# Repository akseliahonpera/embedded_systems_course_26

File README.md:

# embedded_systems_course_26
Repo for embedded systems course project in uni Oulu. Project theme is a drone system.

asdf

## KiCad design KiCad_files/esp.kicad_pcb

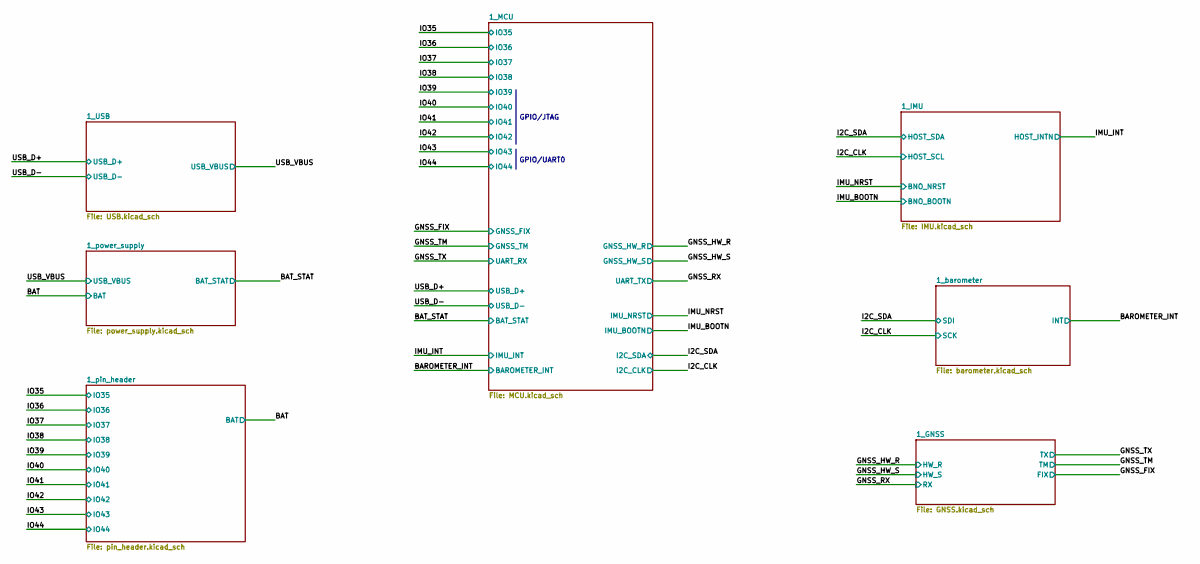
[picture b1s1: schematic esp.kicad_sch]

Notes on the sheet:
GPIO/JTAG
GPIO/UART0

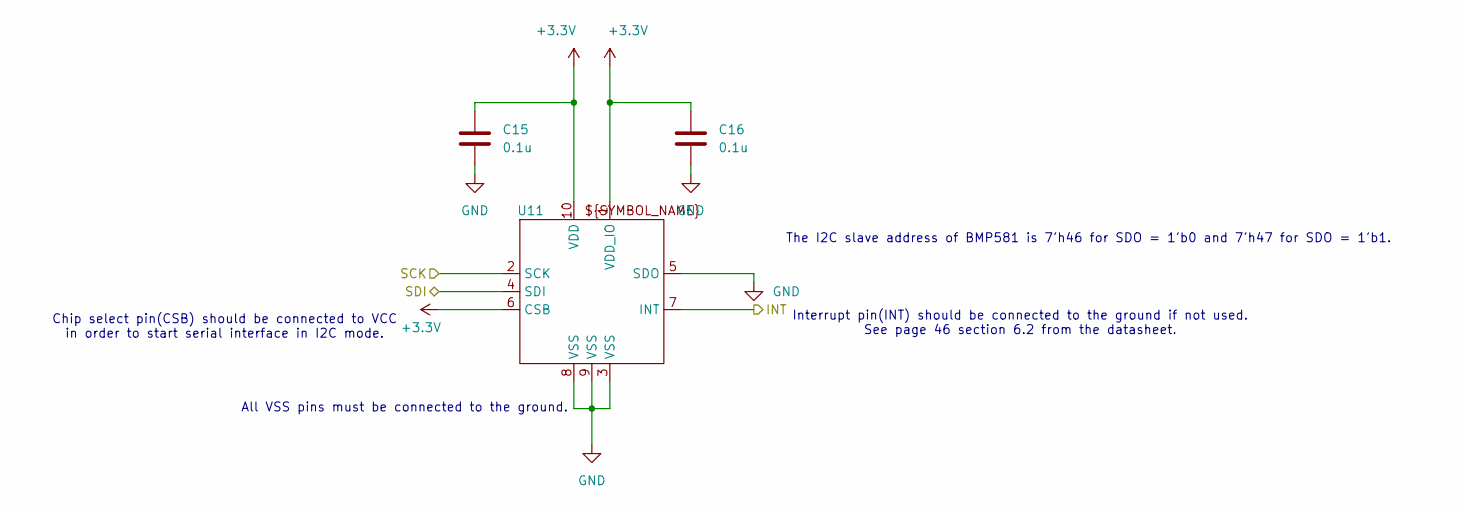
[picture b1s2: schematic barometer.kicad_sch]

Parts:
C15, C16: 0.1u; C_0805_2012Metric_Pad1.18x1.45mm_HandSolder; DigiKey 720-1754-1-ND
U11: QFN10_BMP581_BOS; DigiKey 828-BMP581CT-ND

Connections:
+3.3V: C15.1, C16.1, U11.1 (VDD_IO), U11.6 (CSB), U11.10 (VDD); also elsewhere on the board
/BAROMETER_INT: U11.7 (INT); also elsewhere on the board
/I2C_CLK: U11.2 (SCK); also elsewhere on the board
/I2C_SDA: U11.4 (SDI); also elsewhere on the board
GND: C15.2, C16.2, U11.3 (VSS), U11.5 (SDO), U11.8 (VSS), U11.9 (VSS); also elsewhere on the board

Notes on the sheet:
Chip select pin(CSB) should be connected to VCC in order to start serial interface in I2C mode.
The I2C slave address of BMP581 is 7'h46 for SDO = 1'b0 and 7'h47 for SDO = 1'b1.
All VSS pins must be connected to the ground.
Interrupt pin(INT) should be connected to the ground if not used. See page 46 section 6.2 from the datasheet.

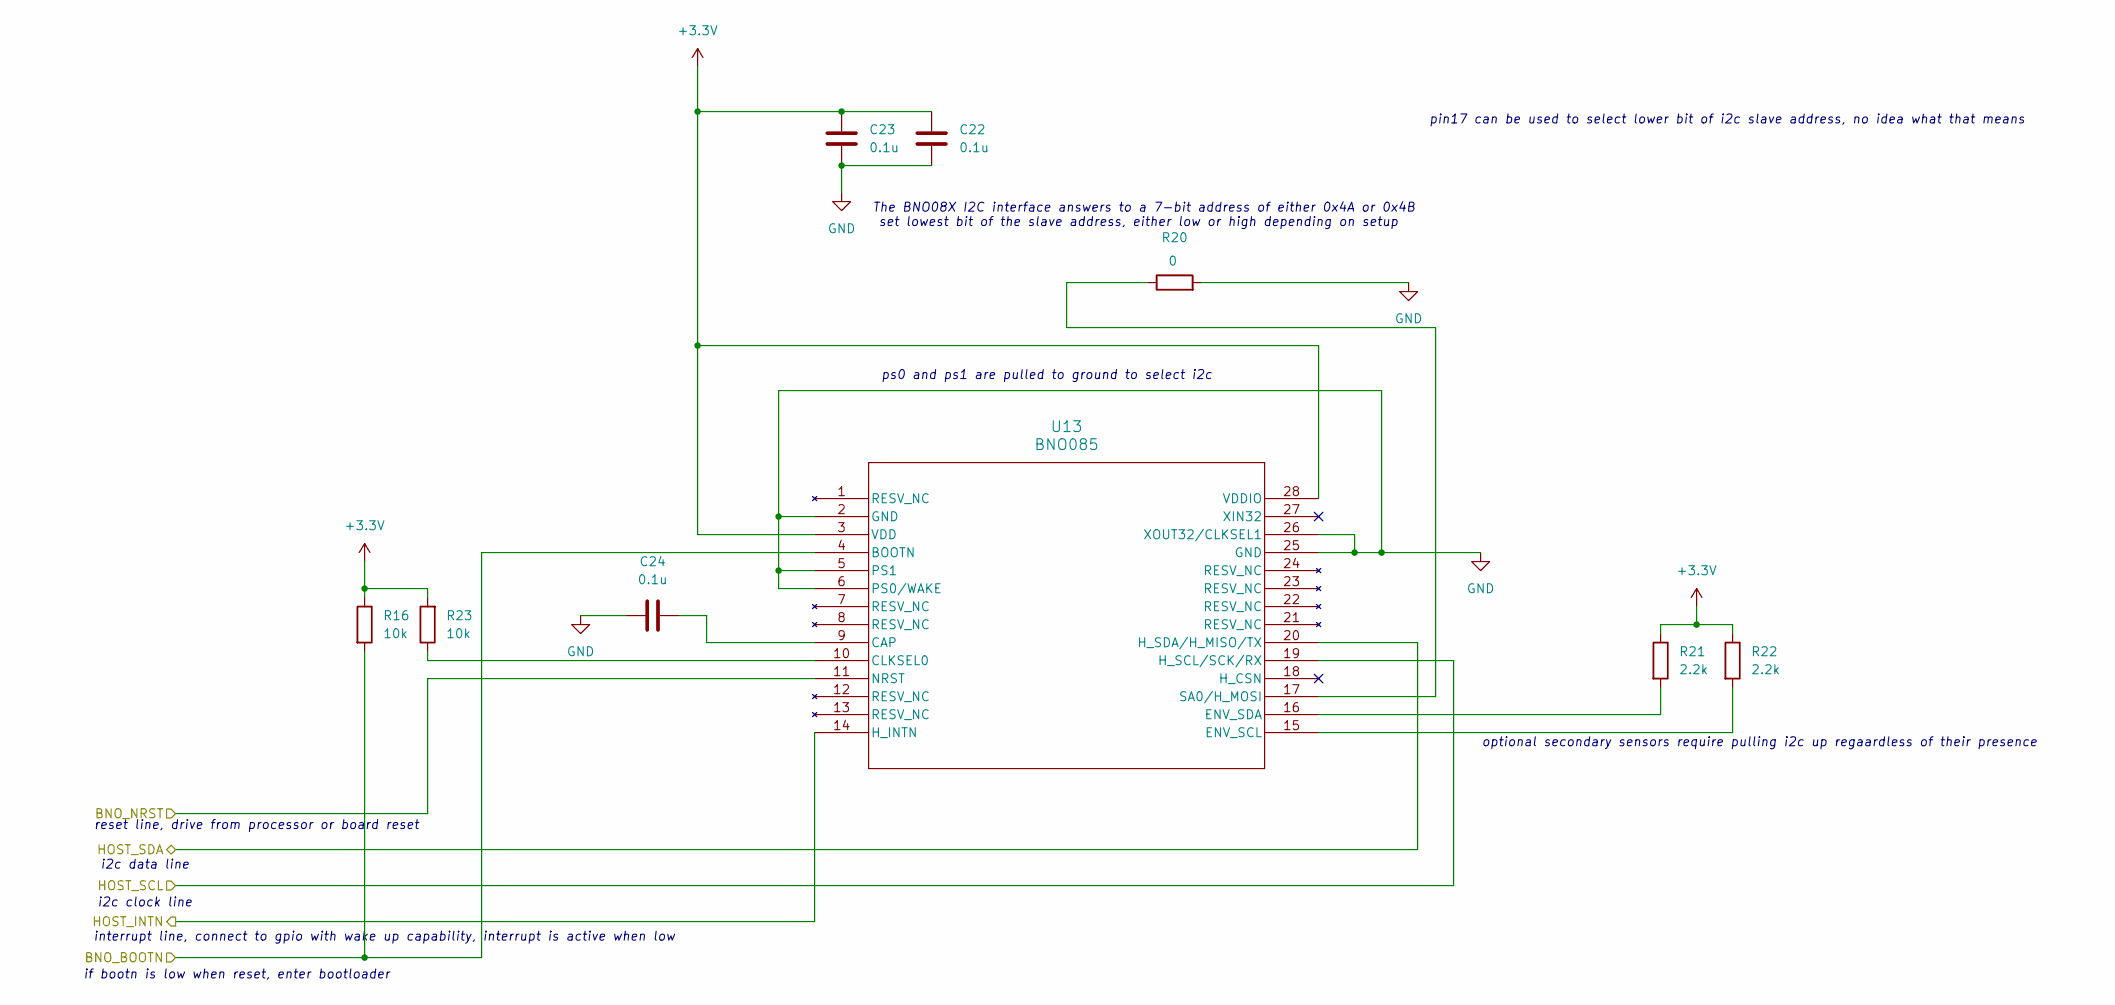
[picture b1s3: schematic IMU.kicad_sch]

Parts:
C22, C23, C24: 0.1u; C_0805_2012Metric_Pad1.18x1.45mm_HandSolder; DigiKey 720-1754-1-ND
R16, R23: 10k; R_0805_2012Metric_Pad1.20x1.40mm_HandSolder; DigiKey 541-10.0KCCT-ND
R20: 0; R_0805_2012Metric_Pad1.20x1.40mm_HandSolder
R21, R22: 2.2k; R_0805_2012Metric_Pad1.20x1.40mm_HandSolder; DigiKey 311-2.20KCRCT-ND
U13: BNO085; DigiKey 1888-1006-1-ND

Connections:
+3.3V: C22.1, C23.1, R16.1, R21.1, R22.1, R23.2, U13.3 (VDD), U13.28 (VDDIO); also elsewhere on the board
/I2C_CLK: U13.19 (H_SCL/SCK/RX); also elsewhere on the board
/I2C_SDA: U13.20 (H_SDA/H_MISO/TX); also elsewhere on the board
/IMU_BOOTN: R16.2, U13.4 (BOOTN); also elsewhere on the board
/IMU_INT: U13.14 (H_INTN); also elsewhere on the board
/IMU_NRST: U13.11 (NRST); also elsewhere on the board
GND: C22.2, C23.2, C24.2, R20.2, U13.2 (GND), U13.5 (PS1), U13.6 (PS0/WAKE), U13.25 (GND), U13.26 (XOUT32/CLKSEL1); also elsewhere on the board
unnamed: C24.1, U13.9 (CAP)
unnamed: R23.1, U13.10 (CLKSEL0)
unnamed: R22.2, U13.15 (ENV_SCL)
unnamed: R21.2, U13.16 (ENV_SDA)
unnamed: R20.1, U13.17 (SA0/H_MOSI)

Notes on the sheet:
ps0 and ps1 are pulled to ground to select i2c
optional secondary sensors require pulling i2c up regaardless of their presence
pin17 can be used to select lower bit of i2c slave address, no idea what that means
i2c clock line
i2c data line
reset line, drive from processor or board reset
set lowest bit of the slave address, either low or high depending on setup
interrupt line, connect to gpio with wake up capability, interrupt is active when low
if bootn is low when reset, enter bootloader
The BNO08X I2C interface answers to a 7-bit address of either 0x4A or 0x4B

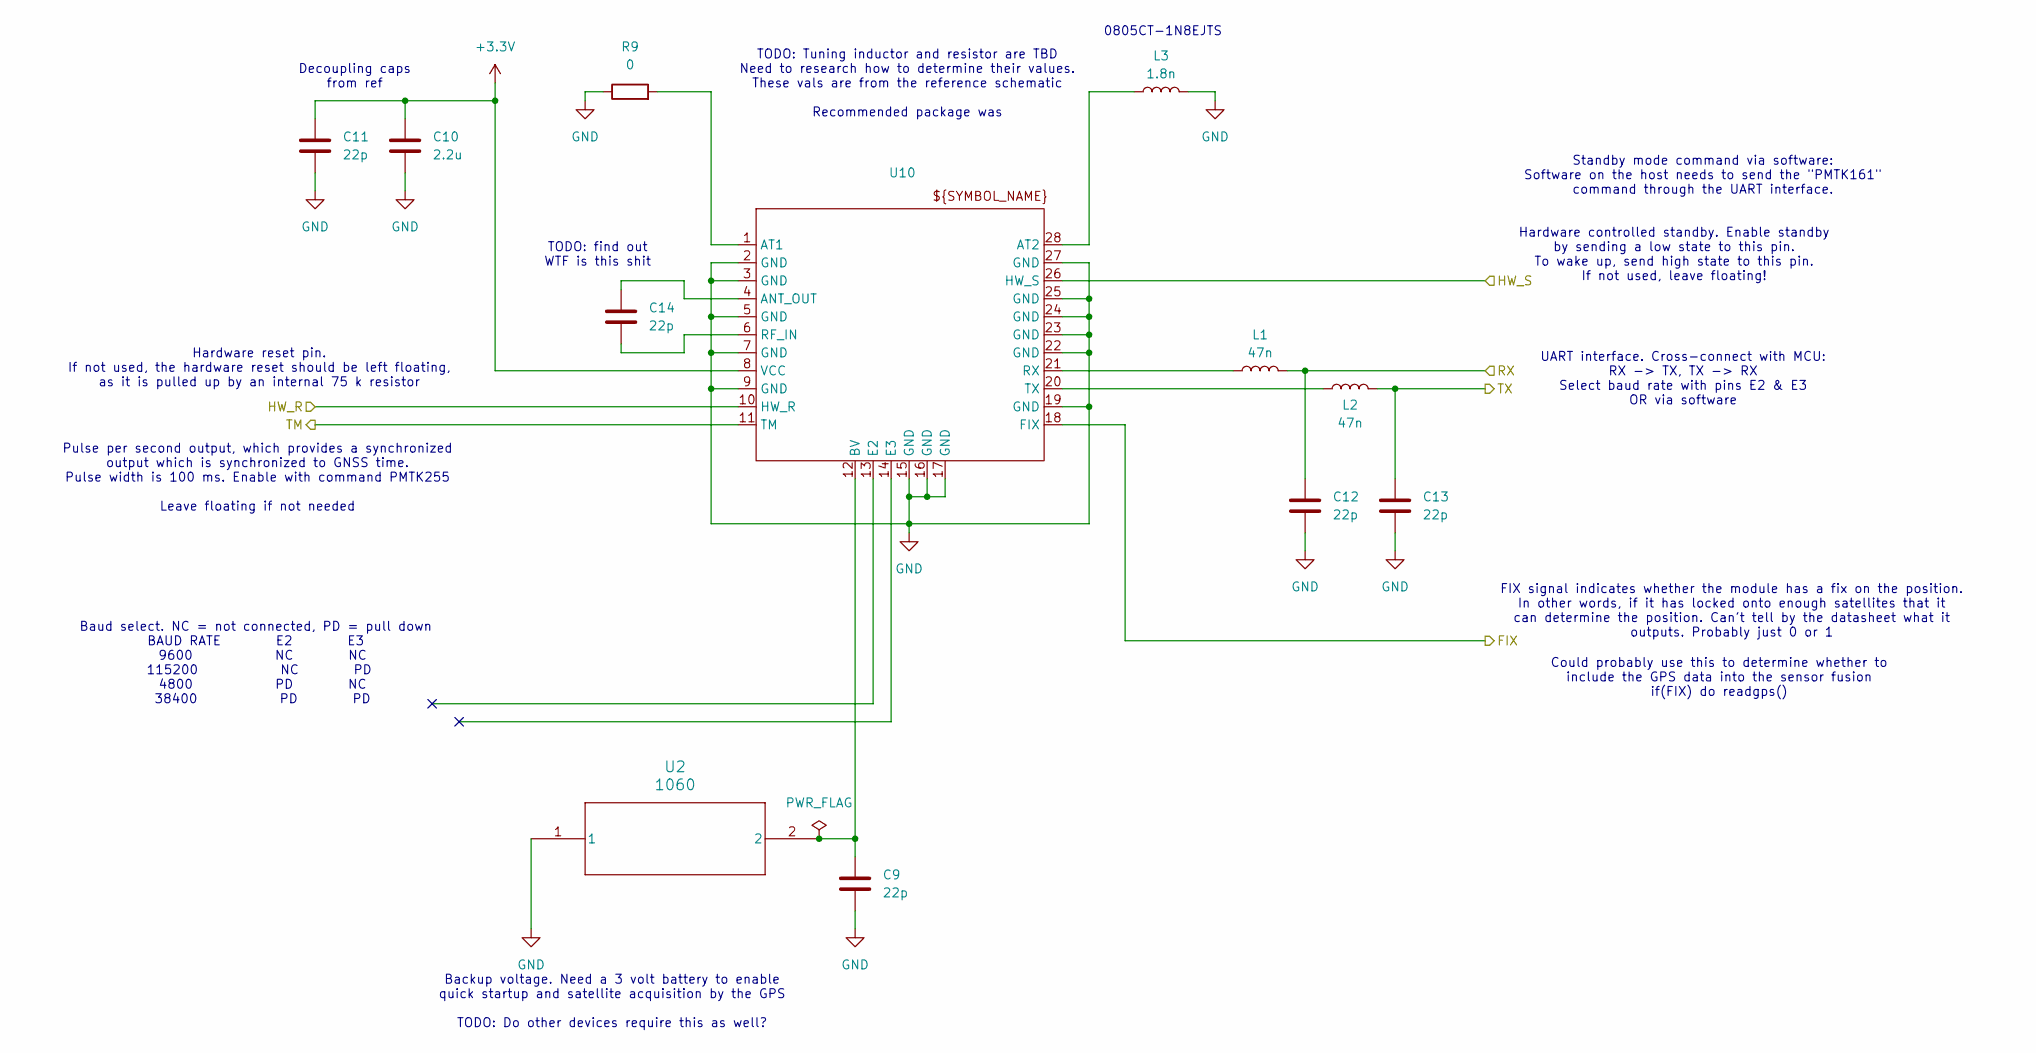
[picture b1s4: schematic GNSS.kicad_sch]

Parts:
C9, C11, C12, C13, C14: 22p; C_0805_2012Metric_Pad1.18x1.45mm_HandSolder; DigiKey 399-17625-1-ND
C10: 2.2u; C_0805_2012Metric_Pad1.18x1.45mm_HandSolder; DigiKey 399-C0805C225K4RACTUCT-ND
L1, L2: 47n; L_0805_2012Metric_Pad1.05x1.20mm_HandSolder; DigiKey 445-1032-1-ND
L3: 1.8n; L_0805_2012Metric_Pad1.05x1.20mm_HandSolder; DigiKey 2035-1135-1-ND
R9: 0; R_0805_2012Metric_Pad1.20x1.40mm_HandSolder; DigiKey 311-0.0ARCT-ND
U2: 1060; 1060_KEY; DigiKey 36-1060-ND
U10: QFN28_M20048-1_ANT; DigiKey 627-1099-1-ND

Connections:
+3.3V: C10.1, C11.1, U10.8 (VCC); also elsewhere on the board
/GNSS_FIX: U10.18 (FIX); also elsewhere on the board
/GNSS_HW_R: U10.10 (HW_R); also elsewhere on the board
/GNSS_HW_S: U10.26 (HW_S); also elsewhere on the board
/GNSS_RX: C12.1, L1.2; also elsewhere on the board
/GNSS_TM: U10.11 (TM); also elsewhere on the board
/GNSS_TX: C13.1, L2.2; also elsewhere on the board
GND: C9.2, C10.2, C11.2, C12.2, C13.2, L3.2, R9.1, U2.1, U10.2 (GND), U10.3 (GND), U10.5 (GND), U10.7 (GND), U10.9 (GND), U10.15 (GND), U10.16 (GND), U10.17 (GND), U10.19 (GND), U10.22 (GND), U10.23 (GND), U10.24 (GND), U10.25 (GND), U10.27 (GND); also elsewhere on the board
unnamed: C14.1, U10.4 (ANT_OUT)
unnamed: R9.2, U10.1 (AT1)
unnamed: L3.1, U10.28 (AT2)
unnamed: C9.1, U2.2, U10.12 (BV)
unnamed: C14.2, U10.6 (RF_IN)
unnamed: L1.1, U10.21 (RX)
unnamed: L2.1, U10.20 (TX)

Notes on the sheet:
Backup voltage. Need a 3 volt battery to enable quick startup and satellite acquisition by the GPS TODO: Do other devices require this as well?
Could probably use this to determine whether to include the GPS data into the sensor fusion if(FIX) do readgps()
UART interface. Cross-connect with MCU: RX -> TX, TX -> RX Select baud rate with pins E2 & E3 OR via software
0805CT-1N8EJTS
Hardware reset pin. If not used, the hardware reset should be left floating, as it is pulled up by an internal 75 k resistor
Baud select. NC = not connected, PD = pull down BAUD RATE E2 E3 9600 NC NC 115200 NC PD 4800 PD NC 38400 PD PD
TODO: Tuning inductor and resistor are TBD Need to research how to determine their values. These vals are from the reference schematic Recommended package was
FIX signal indicates whether the module has a fix on the position. In other words, if it has locked onto enough satellites that it can determine the position. Can't tell by the datasheet what it outputs. Probably just 0 or 1
Pulse per second output, which provides a synchronized output which is synchronized to GNSS time. Pulse width is 100 ms. Enable with command PMTK255 Leave floating if not needed
Hardware controlled standby. Enable standby by sending a low state to this pin. To wake up, send high state to this pin. If not used, leave floating!
Standby mode command via software: Software on the host needs to send the "PMTK161" command through the UART interface.
TODO: find out WTF is this shit
Decoupling caps from ref

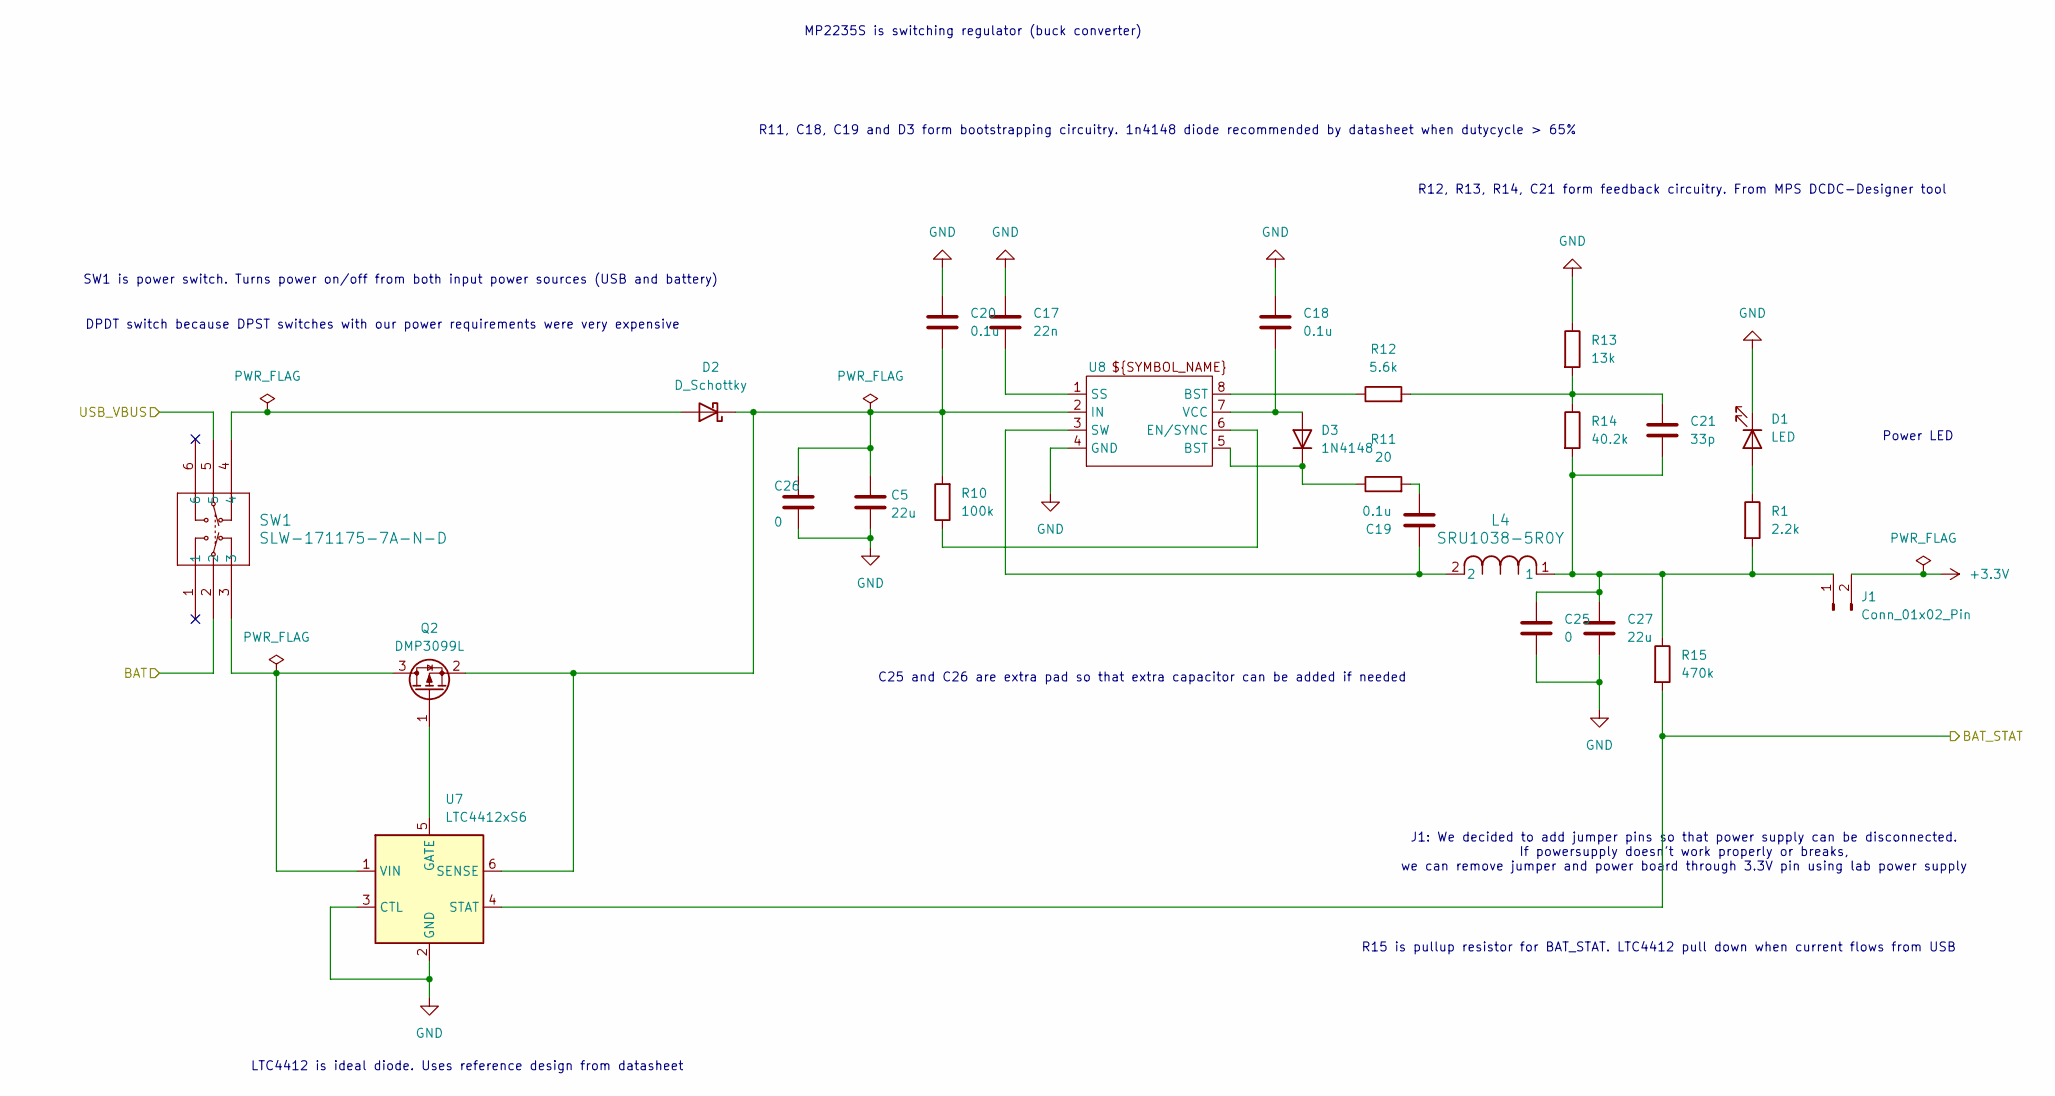
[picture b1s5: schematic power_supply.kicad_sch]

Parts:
C5, C27: 22u; C_1206_3216Metric_Pad1.33x1.80mm_HandSolder; DigiKey 587-3246-1-ND
C17: 22n; C_0805_2012Metric_Pad1.18x1.45mm_HandSolder; DigiKey 490-1644-1-ND
C18, C19, C20: 0.1u; C_0805_2012Metric_Pad1.18x1.45mm_HandSolder; DigiKey 720-1754-1-ND
C21: 33p; C_0805_2012Metric_Pad1.18x1.45mm_HandSolder; DigiKey 399-C0805C330J5GACTUCT-ND
C25, C26: 0; C_1206_3216Metric_Pad1.33x1.80mm_HandSolder
D1: LED; LED_0805_2012Metric_Pad1.15x1.40mm_HandSolder; DigiKey 492-2281-1-ND
D2: D_Schottky; D_SOD-323_HandSoldering; DigiKey CUS10S30H3FCT-ND
D3: 1N4148; D_SOD-323F; DigiKey 1N4148WSFSCT-ND
J1: Conn_01x02_Pin; PinHeader_1x02_P2.54mm_Vertical
L4: SRU1038-5R0Y; IND_BOURNS_SRU1038; DigiKey SRU1038-5R0YCT-ND
Q2: DMP3099L; SOT-23; DigiKey DMP3099L-7DICT-ND
R1: 2.2k; R_0805_2012Metric_Pad1.20x1.40mm_HandSolder; DigiKey 311-2.20KCRCT-ND
R10: 100k; R_0805_2012Metric_Pad1.20x1.40mm_HandSolder; DigiKey 311-100KCRCT-ND
R11: 20; R_0805_2012Metric_Pad1.20x1.40mm_HandSolder; DigiKey 311-20.0CRCT-ND
R12: 5.6k; R_0805_2012Metric_Pad1.20x1.40mm_HandSolder; DigiKey 13-RC0805FR-135K6LCT-ND
R13: 13k; R_0805_2012Metric_Pad1.20x1.40mm_HandSolder; DigiKey 13-RT0805FRE0713KLCT-ND
R14: 40.2k; R_0805_2012Metric_Pad1.20x1.40mm_HandSolder; DigiKey 311-40.2KCRCT-ND
R15: 470k; R_0805_2012Metric_Pad1.20x1.40mm_HandSolder; DigiKey 311-470KCRCT-ND
SW1: SLW-171175-7A-N-D; SLW-171175-7A-N-D_SSD; DigiKey 2223-SLW-171175-7A-N-D-ND
U7: LTC4412xS6; TSOT-23-6; DigiKey 505-LTC4412ES6#TRMPBFCT-ND
U8: TSOT-23-8; DigiKey 1589-1573-1-ND

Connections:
+3.3V: J1.2; also elsewhere on the board
/BAT: SW1.2; also elsewhere on the board
/BAT_STAT: R15.2, U7.4 (STAT); also elsewhere on the board
/USB_VBUS: SW1.5; also elsewhere on the board
GND: C5.2, C17.1, C18.1, C20.1, C25.2, C26.2, C27.2, D1.1 (K), R13.1, U7.2 (GND), U7.3 (CTL), U8.4 (GND); also elsewhere on the board
unnamed: C19.2, R11.2
unnamed: C21.1, R12.2, R13.2, R14.1
unnamed: D1.2 (A), R1.1
unnamed: D2.2 (A), SW1.4
unnamed: C5.1, C20.2, C26.1, D2.1 (K), Q2.2 (S), R10.2, U7.6 (SENSE), U8.2 (IN)
unnamed: C18.2, D3.2 (A), U8.7 (VCC)
unnamed: D3.1 (K), R11.1, U8.5 (BST)
unnamed: C21.2, C25.1, C27.1, J1.1, L4.1, R1.2, R14.2, R15.1
unnamed: Q2.3 (D), SW1.3, U7.1 (VIN)
unnamed: Q2.1 (G), U7.5 (GATE)
unnamed: R12.1, U8.8 (BST)
unnamed: R10.1, U8.6 (EN/SYNC)
unnamed: C17.2, U8.1 (SS)
unnamed: C19.1, L4.2, U8.3 (SW)

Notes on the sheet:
C25 and C26 are extra pad so that extra capacitor can be added if needed
SW1 is power switch. Turns power on/off from both input power sources (USB and battery)
R12, R13, R14, C21 form feedback circuitry. From MPS DCDC-Designer tool
R11, C18, C19 and D3 form bootstrapping circuitry. 1n4148 diode recommended by datasheet when dutycycle > 65%
Power LED
R15 is pullup resistor for BAT_STAT. LTC4412 pull down when current flows from USB
LTC4412 is ideal diode. Uses reference design from datasheet
J1: We decided to add jumper pins so that power supply can be disconnected. If powersupply doesn't work properly or breaks, we can remove jumper and power board through 3.3V pin using lab power supply
MP2235S is switching regulator (buck converter)
DPDT switch because DPST switches with our power requirements were very expensive

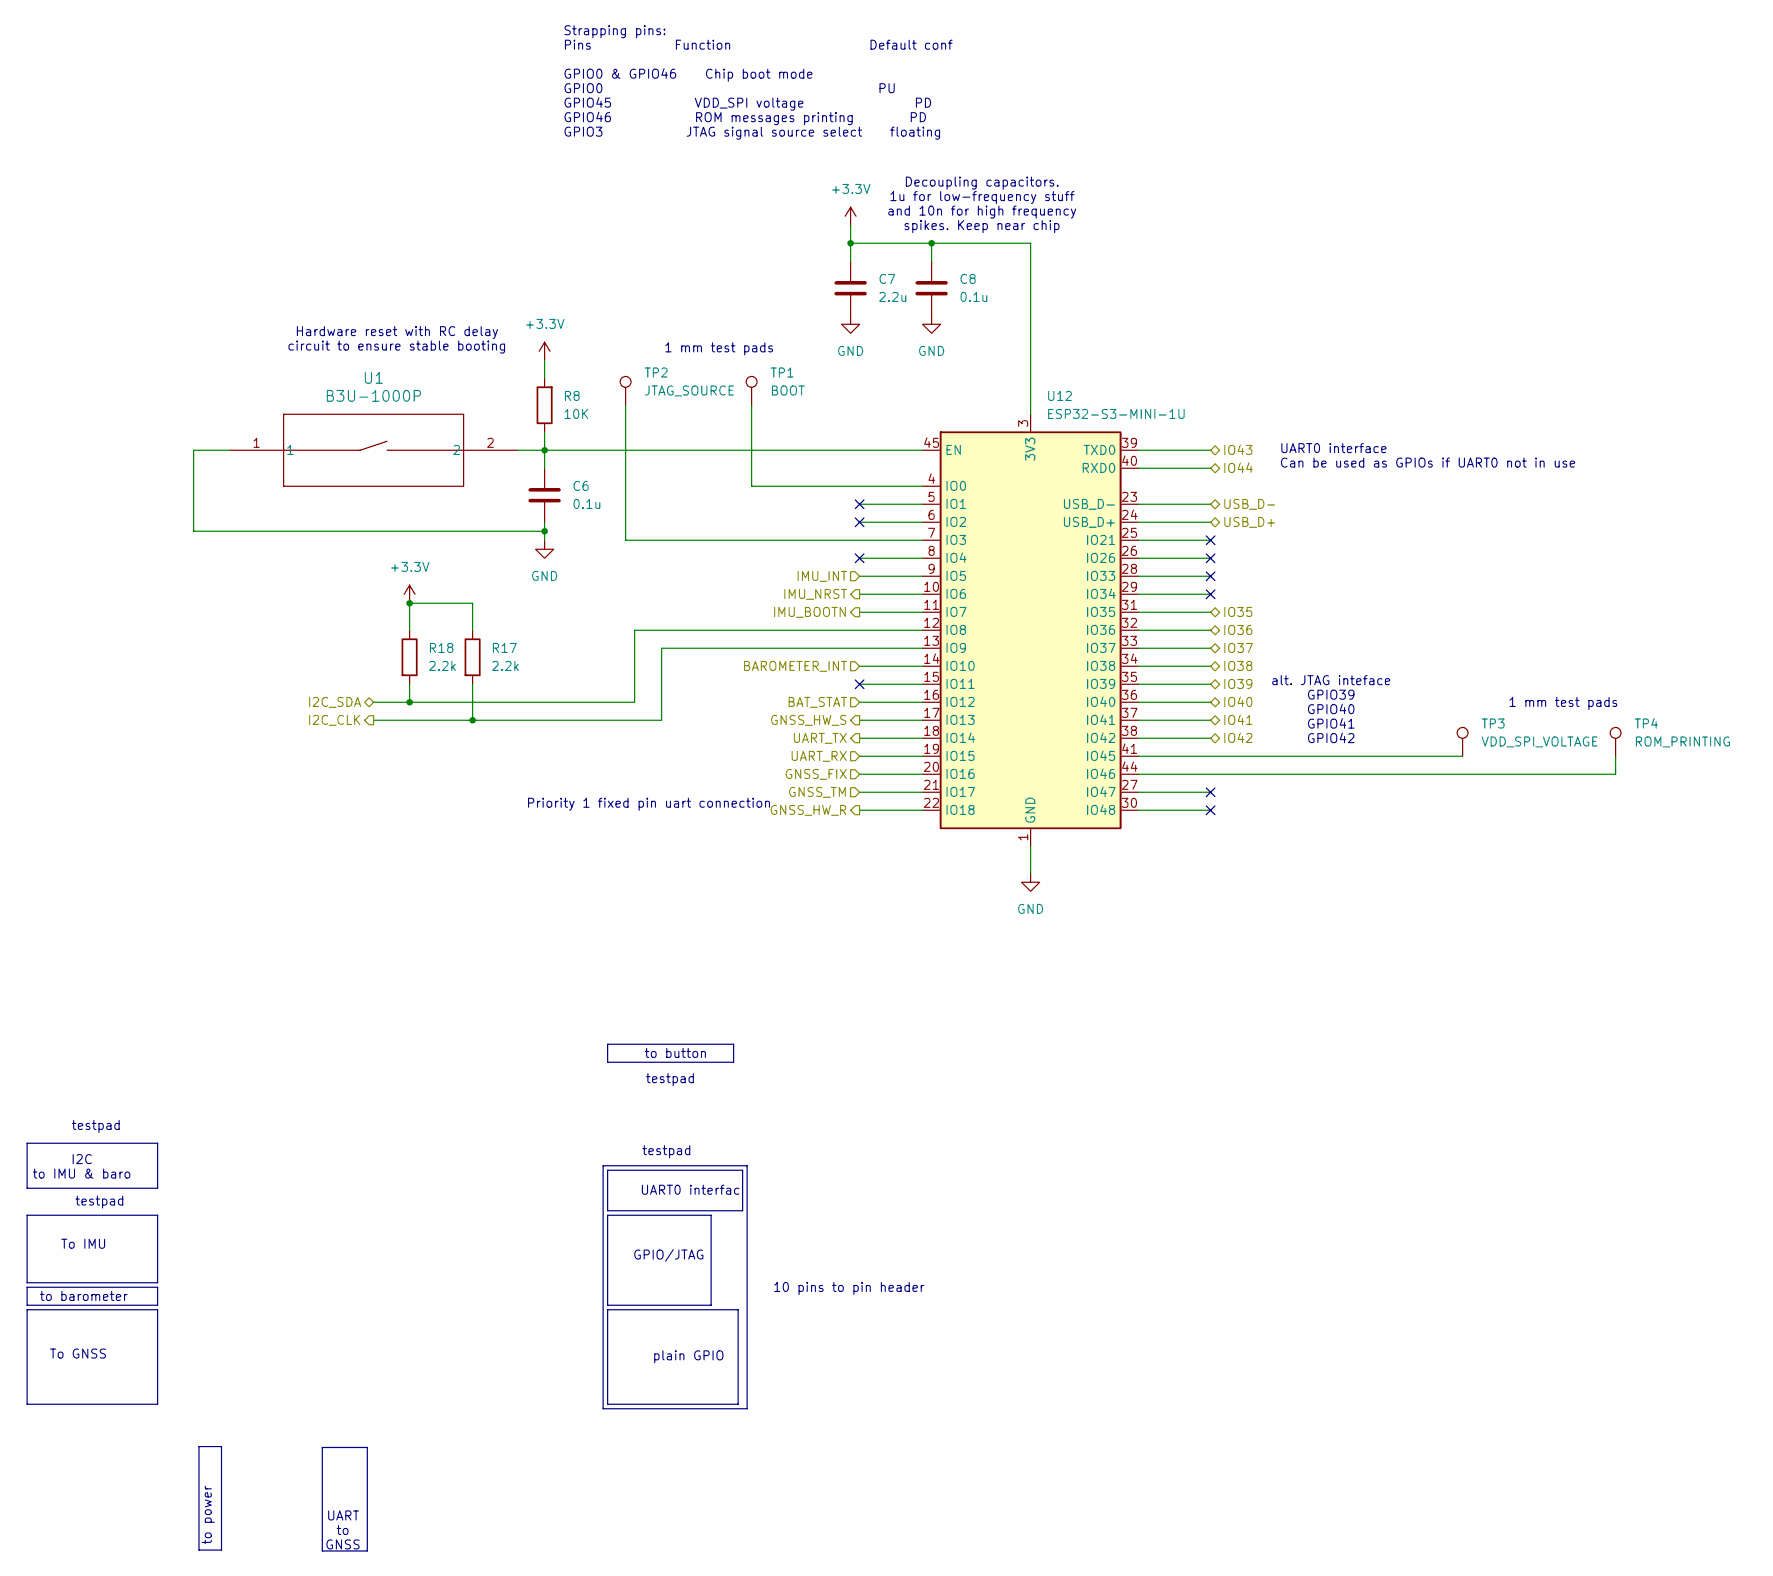
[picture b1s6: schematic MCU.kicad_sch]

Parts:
C6, C8: 0.1u; C_0805_2012Metric_Pad1.18x1.45mm_HandSolder; DigiKey 720-1754-1-ND
C7: 2.2u; C_0805_2012Metric_Pad1.18x1.45mm_HandSolder; DigiKey 399-C0805C225K4RACTUCT-ND
R8: 10K; R_0805_2012Metric_Pad1.20x1.40mm_HandSolder; DigiKey 541-10.0KCCT-ND
R17, R18: 2.2k; R_0805_2012Metric_Pad1.20x1.40mm_HandSolder; DigiKey 311-2.20KCRCT-ND
TP1: BOOT; TestPoint_Pad_D1.0mm
TP2: JTAG_SOURCE; TestPoint_Pad_D1.0mm
TP3: VDD_SPI_VOLTAGE; TestPoint_Pad_D1.0mm
TP4: ROM_PRINTING; TestPoint_Pad_D1.0mm
U1: B3U-1000P; DigiKey SW1020CT-ND
U12: ESP32-S3-MINI-1U; ESP32-S2-MINI-1U; DigiKey 1965-ESP32-S3-MINI-1U-N8CT-ND

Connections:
+3.3V: C7.1, C8.1, R8.2, R17.1, R18.1, U12.3 (3V3); also elsewhere on the board
/BAROMETER_INT: U12.14 (IO10); also elsewhere on the board
/BAT_STAT: U12.16 (IO12); also elsewhere on the board
/GNSS_FIX: U12.20 (IO16); also elsewhere on the board
/GNSS_HW_R: U12.22 (IO18); also elsewhere on the board
/GNSS_HW_S: U12.17 (IO13); also elsewhere on the board
/GNSS_RX: U12.18 (IO14); also elsewhere on the board
/GNSS_TM: U12.21 (IO17); also elsewhere on the board
/GNSS_TX: U12.19 (IO15); also elsewhere on the board
/I2C_CLK: R17.2, U12.13 (IO9); also elsewhere on the board
/I2C_SDA: R18.2, U12.12 (IO8); also elsewhere on the board
/IMU_BOOTN: U12.11 (IO7); also elsewhere on the board
/IMU_INT: U12.9 (IO5); also elsewhere on the board
/IMU_NRST: U12.10 (IO6); also elsewhere on the board
/IO35: U12.31 (IO35); also elsewhere on the board
/IO36: U12.32 (IO36); also elsewhere on the board
/IO37: U12.33 (IO37); also elsewhere on the board
/IO38: U12.34 (IO38); also elsewhere on the board
/IO39: U12.35 (IO39); also elsewhere on the board
/IO40: U12.36 (IO40); also elsewhere on the board
/IO41: U12.37 (IO41); also elsewhere on the board
/IO42: U12.38 (IO42); also elsewhere on the board
/IO43: U12.39 (TXD0); also elsewhere on the board
/IO44: U12.40 (RXD0); also elsewhere on the board
/USB_D+: U12.24 (USB_D+); also elsewhere on the board
/USB_D-: U12.23 (USB_D-); also elsewhere on the board
GND: C6.2, C7.2, C8.2, U1.1, U12.1 (GND), U12.2 (GND), U12.42 (GND), U12.43 (GND), U12.46 (GND), U12.47 (GND), U12.48 (GND), U12.49 (GND), U12.50 (GND), U12.51 (GND), U12.52 (GND), U12.53 (GND), U12.54 (GND), U12.55 (GND), U12.56 (GND), U12.57 (GND), U12.58 (GND), U12.59 (GND), U12.60 (GND), U12.61 (GND), U12.62 (GND), U12.63 (GND), U12.64 (GND), U12.65 (GND); also elsewhere on the board
unnamed: C6.1, R8.1, U1.2, U12.45 (EN)
unnamed: TP1.1, U12.4 (IO0)
unnamed: TP2.1, U12.7 (IO3)
unnamed: TP3.1, U12.41 (IO45)
unnamed: TP4.1, U12.44 (IO46)

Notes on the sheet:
Priority 1 fixed pin uart connection
1 mm test pads
I2C to IMU & baro
GPIO/JTAG
testpad
to power
Hardware reset with RC delay circuit to ensure stable booting
plain GPIO
alt. JTAG inteface GPIO39 GPIO40 GPIO41 GPIO42
Decoupling capacitors. 1u for low-frequency stuff and 10n for high frequency spikes. Keep near chip
UART to GNSS
To GNSS
UART0 interface Can be used as GPIOs if UART0 not in use
To IMU
UART0 interfac
10 pins to pin header
to button
Strapping pins: Pins Function Default conf GPIO0 & GPIO46 Chip boot mode GPIO0 PU GPIO45 VDD_SPI voltage PD GPIO46 ROM messages printing PD GPIO3 JTAG signal source select floating
to barometer

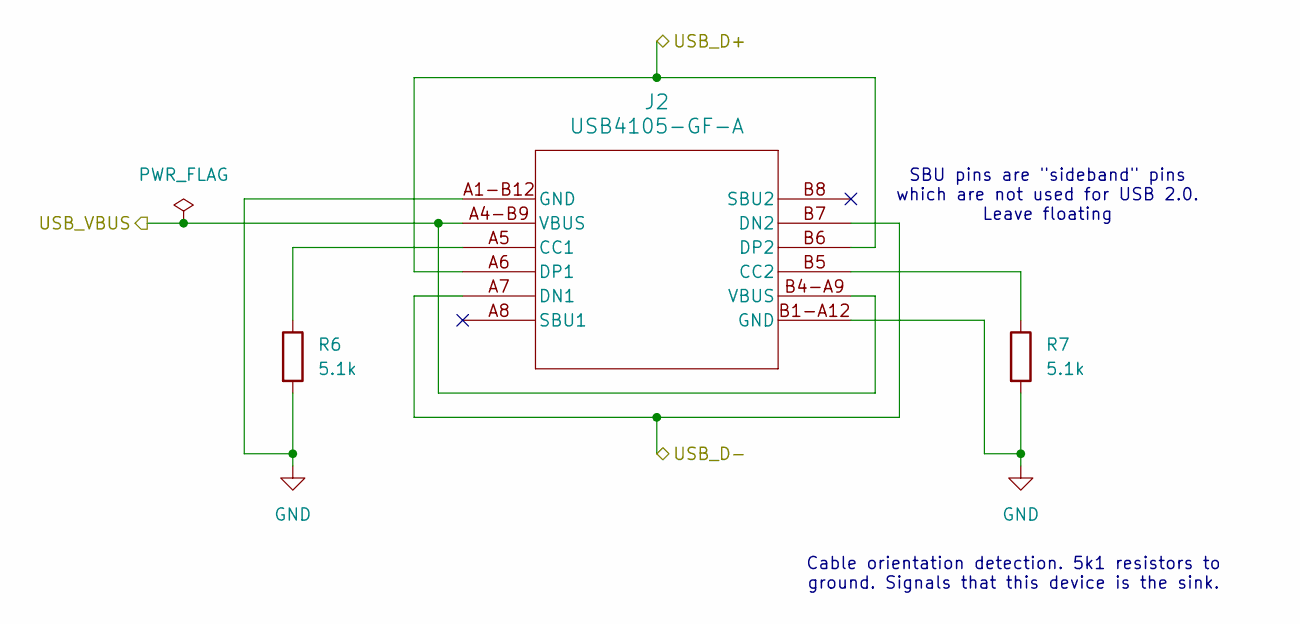
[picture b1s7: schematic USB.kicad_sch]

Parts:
J2: USB4105-GF-A; USB4105_GCT; DigiKey 2073-USB4105-GF-ACT-ND
R6, R7: 5.1k; R_0805_2012Metric_Pad1.20x1.40mm_HandSolder; DigiKey P5.1KDACT-ND

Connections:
/USB_D+: J2.A6 (DP1), J2.B6 (DP2); also elsewhere on the board
/USB_D-: J2.A7 (DN1), J2.B7 (DN2); also elsewhere on the board
/USB_VBUS: J2.A4-B9 (VBUS), J2.B4-A9 (VBUS); also elsewhere on the board
GND: J2.A1-B12 (GND), J2.B1-A12 (GND), R6.2, R7.2; also elsewhere on the board
unnamed: J2.A5 (CC1), R6.1
unnamed: J2.B5 (CC2), R7.1

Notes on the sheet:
Cable orientation detection. 5k1 resistors to ground. Signals that this device is the sink.
SBU pins are "sideband" pins which are not used for USB 2.0. Leave floating

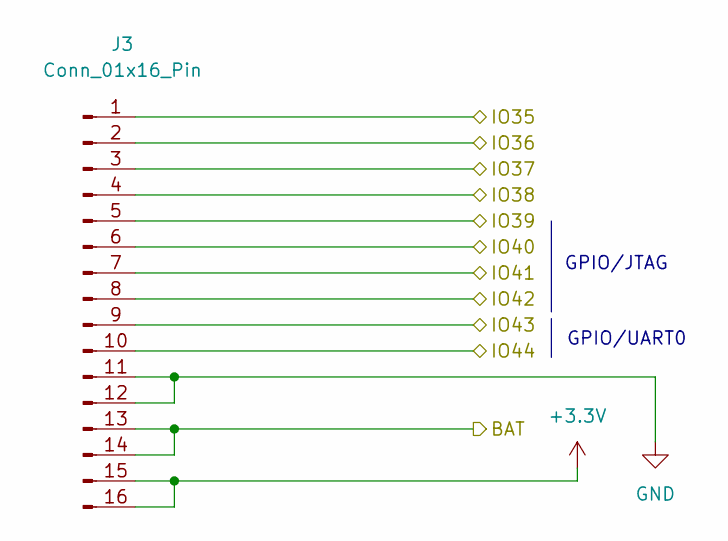
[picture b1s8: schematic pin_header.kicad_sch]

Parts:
J3: Conn_01x16_Pin; PinHeader_1x16_P2.54mm_Vertical

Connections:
+3.3V: J3.15, J3.16; also elsewhere on the board
/BAT: J3.13, J3.14; also elsewhere on the board
/IO35: J3.1; also elsewhere on the board
/IO36: J3.2; also elsewhere on the board
/IO37: J3.3; also elsewhere on the board
/IO38: J3.4; also elsewhere on the board
/IO39: J3.5; also elsewhere on the board
/IO40: J3.6; also elsewhere on the board
/IO41: J3.7; also elsewhere on the board
/IO42: J3.8; also elsewhere on the board
/IO43: J3.9; also elsewhere on the board
/IO44: J3.10; also elsewhere on the board
GND: J3.11, J3.12; also elsewhere on the board

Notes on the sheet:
GPIO/UART0
GPIO/JTAG

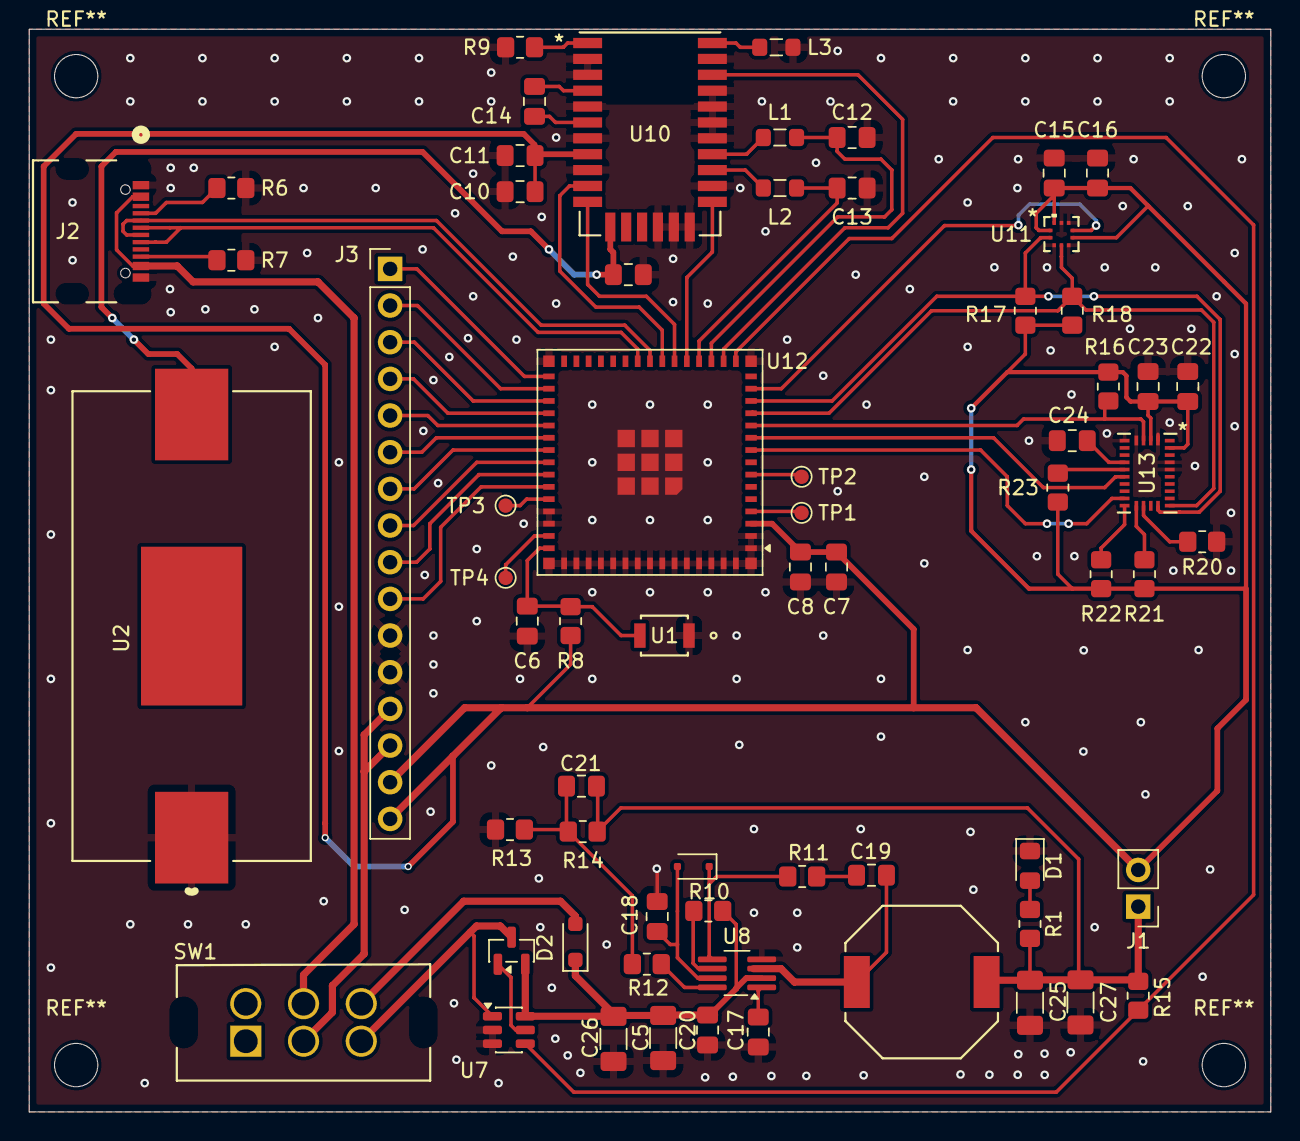
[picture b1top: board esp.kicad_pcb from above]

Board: 2 copper layers, 86.0 x 75.0 mm, 65 parts (0 on the bottom side), 62 nets.

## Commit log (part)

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2026-03-03 KiCad prokkis
2026-03-03 Update .gitignore for KiCAD project files
    Ignoret lisätty kicad projektia varten
2026-03-03 Tyhjät footprintit ja symbolit lisätty komponenteille jotka tarvitsee luoda itse
2026-03-03 tyhjät symboolit
2026-03-03 symbolit tehty puuttuville komponenteille
2026-03-04 Pari komponenttia powerille
2026-03-04 konffit kuntoon
2026-03-06 hierarchical_sheets
2026-03-06 buck converter reference design
2026-03-06 GNSS aloitettu
2026-03-07 GNSS WIP
2026-03-08 barometri
2026-03-08 interrupt output
2026-03-08 BNO085 lisätty kirjastoon
2026-03-08 power supply
2026-03-09 hierarkiset pinnit poweriin
2026-03-09 IMU schematic drawn
2026-03-09 tekstiä
2026-03-11 fadsf
2026-03-12 mohloilut korjattu
2026-03-12 sadfsadf
2026-03-12 saatana
2026-03-12 footprinttejä
2026-03-12 footprints for powersupply
2026-03-12 power led
2026-03-12 taikinointia
2026-03-12 footprinttejä komponenteille + kapasitanssit korjattu imusta
2026-03-12 digikey field for power supply components
2026-03-12 ajan tasalle
2026-03-12 paristo lisätty
2026-03-12 pin header
2026-03-12 c5 korjattu
2026-03-12 välipusku
2026-03-12 imu johot
2026-03-12 hähää
2026-03-12 sdfasa
2026-03-12 puskee
2026-03-12 johtoja
2026-03-13 yksi johto paremmin
2026-03-13 pinnit
2026-03-13 piuhat vedetty mculla ja i2c pullupit mculle
2026-03-13 pwr_flags
2026-03-13 JTAG
2026-03-13 dpdt switch
2026-03-13 pom päivetty
2026-03-13 ERC hiljennetty
2026-03-17 comments
2026-03-23 more comments
2026-03-23 everything in single sheet
2026-04-02 headerit mietitty, pinnijärjestystä muutettu mcussa
2026-04-02 UART1 siirretty parempaan paikkaan
2026-04-02 powersupply pcb
2026-04-02 imu pcb v1
2026-04-02 imu pcb v1_
2026-04-02 jumper pins for disconnecting power supply
2026-04-03 gepsiä alotettu
2026-04-06 wippistä
2026-04-07 power supply to pcb
2026-04-07 liitoksia
2026-04-07 wider GND traces on power supply
2026-04-07 backside GND fill
2026-04-07 all connected for now
2026-04-07 wider power trace for MCU
2026-04-07 copper fillin minimietäisyys laskettu vastaamaan valmistajan speksiä, vioja yms
2026-04-10 siivoilua
2026-04-10 gerberit
2026-04-10 gerberit 2. yritys
2026-04-10 korjattu
2026-04-10 power supply FB circuitry to better place
2026-04-10 barometri interrupt viety muualta kuin sirun alta
2026-04-10 fixed via positions and power trace width
2026-04-12 more vias close to USB GNDs
2026-04-12 changed voltage regulator footprint
2026-04-12 new gerber zip
2026-06-12 projekti template
2026-06-12 barometri poweri testiä
2026-06-12 rename to main.c
